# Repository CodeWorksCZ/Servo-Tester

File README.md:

# Servo Tester

> **Work In Progress (WIP):** This project is under active development.  
> Features, wiring, and behavior may change between commits.

RC servo tester for Arduino Pro Mini (ATmega328P, 16 MHz) with OLED UI, settings in EEPROM, and 3-channel current monitoring via INA3221.

User manual: `MANUAL.md`

## Features

- Servo control modes: `POT`, `CENTER`, `SWEEP`
- OLED screens: `STATUS`, `GAUGE`, `CURRENT`, `VBUS`, `PEAK`
- SWEEP cycle counter shown only in SWEEP mode
- Settings menu with EEPROM persistence
- INA3221 current measurement on 3 channels
- INA3221 bus voltage and droop (`dV`) view per channel
- INA3221 per-channel warning/critical current alerts (`WR`/`CR`)
- Optional alert LED output when any channel is in `WR` or `CR`
- Optional STD/HV mode indicator LEDs
- LED startup self-test
- Automatic unit display (`mA` / `A`) on current screens
- Servo rail mode detection (`STD` / `HV`) from ADC voltage sensing on `A1`
- Compile-time UI language selection through `include/config.h` and `include/lang.h`
- Minimal serial debug line for INA3221 communication check at boot

## Controls

- `SELECT` short press: switch LCD screen (`STATUS -> GAUGE -> CURRENT -> VBUS -> PEAK`)
- `SELECT` long press: enter settings menu
- `UP` / `DOWN` in status mode: change control mode (`POT`, `CENTER`, `SWEEP`)
- `UP` / `DOWN` in menu: navigate items or change value
- `SELECT` in menu: confirm

## Settings Menu

- `Min pulse` (us)
- `Max pulse` (us)
- `Reverse`
- `Sweep cycle` (0.5-10.0 s, default 3.0 s)
- `Burn cycles` (`0` = infinite SWEEP, otherwise stop after selected cycle count)
- `Save & exit`
- `Cancel`

## Pin Mapping (Default)

| Arduino Pin | Config Name | Function |
| --- | --- | --- |
| `D2` | `BTN_UP_PIN` | UP button |
| `D3` | `BTN_DOWN_PIN` | DOWN button |
| `D4` | `ALERT_LED_PIN` | Optional INA3221 warning/critical alert LED |
| `D5` | `BTN_SELECT_PIN` | SELECT button |
| `D6` | `SERVO_PIN` | Servo signal output |
| `D7` | `STD_MODE_LED_PIN` | STD servo rail indicator LED |
| `D8` | `HV_MODE_LED_PIN` | HV servo rail indicator LED |
| `D9` | `OLED_CLK` | OLED clock (`CLK` / `D0`) |
| `D10` | `OLED_MOSI` | OLED data (`MOSI` / `DIN` / `D1`) |
| `D11` | `OLED_RESET` | OLED reset |
| `D12` | `OLED_DC` | OLED data/command |
| `D13` | `OLED_CS` | OLED chip select |
| `A0` | `POT_PIN` | Servo control potentiometer |
| `A1` | `SERVO_VSENSE_PIN` | Servo rail voltage sensing through divider |
| `A4` | I2C `SDA` | INA3221 data |
| `A5` | I2C `SCL` | INA3221 clock |

Full mapping is in `pins.txt`.

## Configuration

Main configuration is in `include/config.h`.

You can adjust:

- UI language (`SERVO_TESTER_LANGUAGE`)
- pin assignments
- button debounce and long-press timing
- servo pulse limits and step size
- sweep timing and limits
- burn-in cycle count limits
- INA3221 shunt values and calibration factors
- ADC divider and HV threshold
- LED polarity and optional LED outputs

### UI Language

The UI language is selected at compile time to keep flash usage low:

```cpp
#define SERVO_TESTER_LANGUAGE SERVO_TESTER_LANG_EN
```

Available options:

- `SERVO_TESTER_LANG_EN`
- `SERVO_TESTER_LANG_CZ`

Text resources are stored in `include/lang.h`. Only the selected language is compiled into the firmware.

### Serial Debug

When `SERIAL_DEBUG_ENABLED` is enabled, the firmware prints one INA3221 status line after boot at `115200 baud`:

- `INA3221 OK`
- `INA3221 NOT FOUND`

This is intended only as a simple wiring/communication check.

## Build

PlatformIO environment:

- file: `platformio.ini`
- env: `pro16MHzatmega328`

Libraries used:

- Adafruit SSD1306
- Adafruit GFX Library
- Adafruit INA3221 Library
- Servo

## Project Layout

- `src/main.cpp`: entry point (`setup` / `loop`)
- `src/app_controller.*`: app state machine and high-level control flow
- `src/display_ui.*`: OLED rendering
- `src/ina_monitor.*`: INA3221 handling and peak tracking
- `src/button_input.*`: button debounce and short/long press events
- `src/settings_store.*`: EEPROM load/save/validation
- `src/app_types.h`: shared app structs/enums
- `hardware/Kicad/Servo Tester/`: KiCad project files for PCB/schematic
- `hardware/Schematics/`: exported schematic PDFs
- `hardware/Datasheets/`: component datasheets
- `hardware/enclosure/`: 3D printed enclosure files and notes

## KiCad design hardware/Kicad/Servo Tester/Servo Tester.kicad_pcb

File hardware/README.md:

# Hardware Notes (WIP)

This folder contains schematics/PCB files for the Servo Tester hardware.

## Pre-Layout Checklist

- Keep logic rail (`VCC` for Pro Mini + OLED + INA3221) separate from servo power rail.
- Do not feed logic directly from HV servo rail.
- Use a common GND, but route high-current servo return separately and join at one star point.

## Servo Power Protection

- Add bulk capacitor on servo rail input: `470-1000 uF` (low-ESR, voltage rating for your rail).
- Add local decoupling near each servo connector: `100 nF` from `+BATT` to `GND`.
- Add TVS diode across servo rail (`+BATT` to `GND`) near power entry.
- Add PTC fuse in series with servo rail input.

## INA3221 Current Measurement

- Place shunts in series with servo `+` path only.
- Route INA sense lines as Kelvin connections directly to shunt pads.
- For channels that may stay unconnected, add `100k` between `INx+` and `INx-` to reduce floating behavior.
- For `R100` shunts (`0.1 ohm`), keep alert thresholds below ~`1.64 A`.

## Servo Signal Robustness

- Add series resistor on each servo signal line: `220-470 ohm` (`330 ohm` recommended).
- Keep signal and GND return close together in routing/connectors.

## Connector Safety

- Prefer keyed/polarized connectors where possible.
- If using standard 3-pin servo headers, clearly mark `SIG`, `+`, `-` on silkscreen.

## Firmware-Coupled Pins (Current Config)

- `D6`: Servo PWM output
- `D4`: Alert LED output
- `A4/A5`: INA3221 I2C
- `A0`: Potentiometer input
- `A1`: Servo rail voltage sense

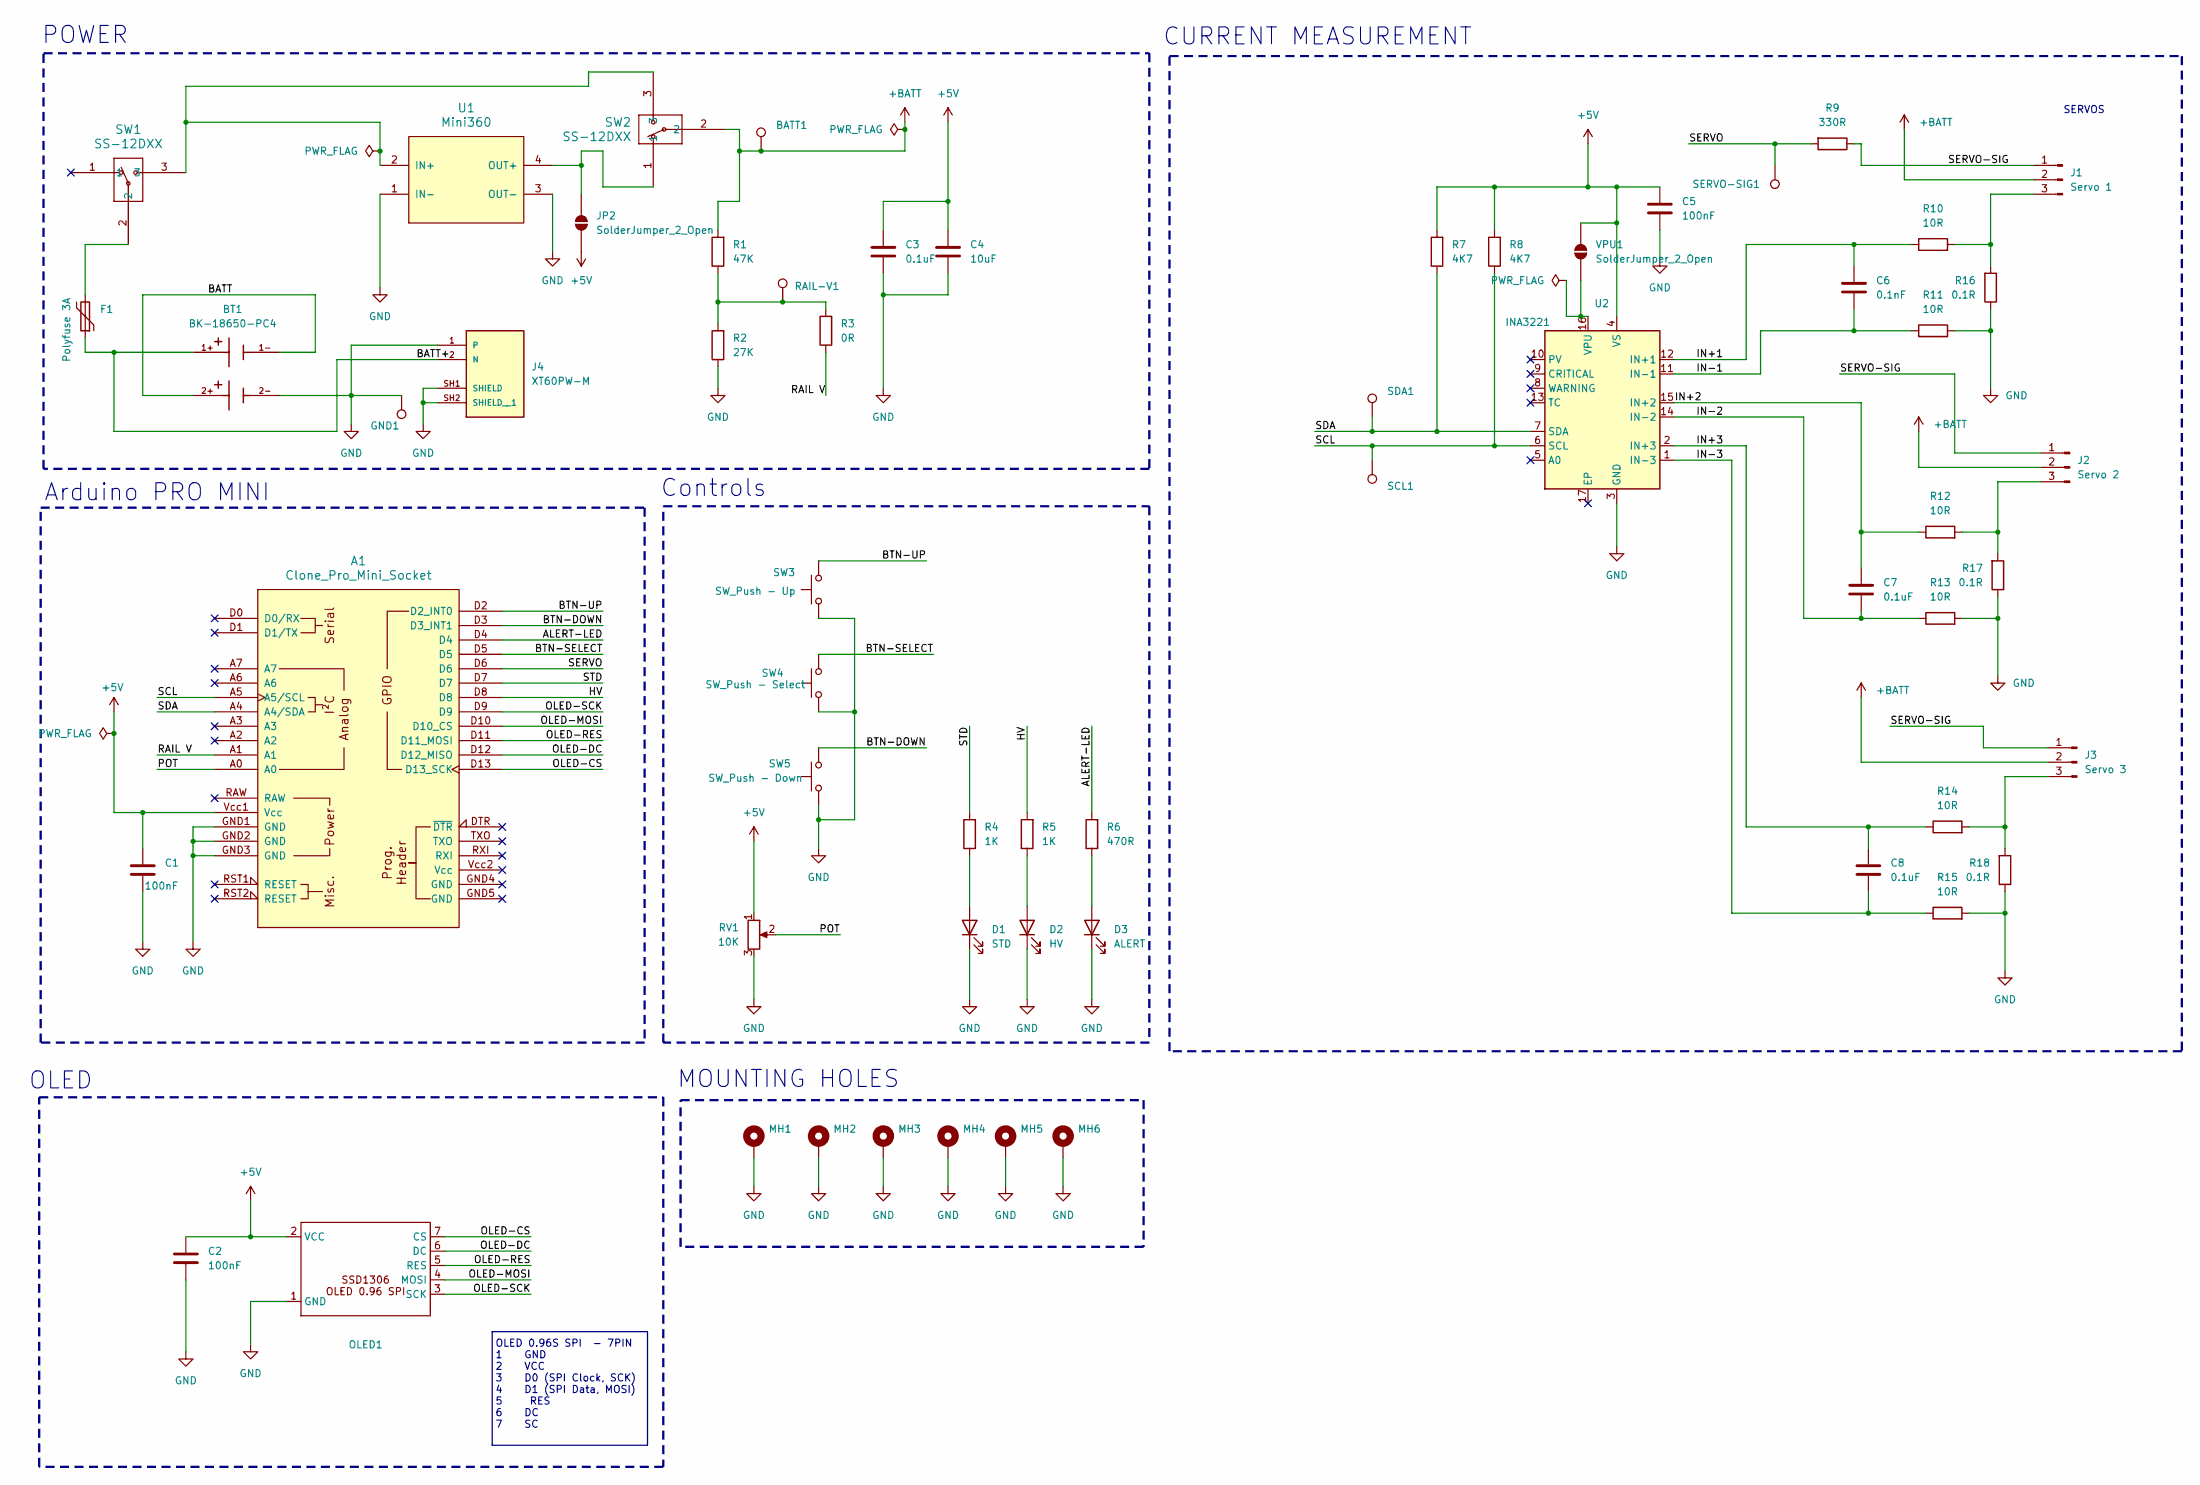
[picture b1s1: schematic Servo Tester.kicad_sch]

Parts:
A1: Clone_Pro_Mini_Socket; Clone_Pro_Mini_Socket_No_PROG
BATT1: TestPoint; TestPoint_Pad_D2.0mm
BT1: BK-18650-PC4; BAT_BK-18650-PC4; PARTREV K
C1, C2, C5: 100nF; C_0805_2012Metric
C3, C7, C8: 0.1uF; C_0805_2012Metric
C4: 10uF; C_0805_2012Metric
C6: 0.1nF; C_0805_2012Metric
D1: STD; LED_D3.0mm
D2: HV; LED_D3.0mm
D3: ALERT; LED_D3.0mm
F1: Polyfuse 3A; Fuse_LittleFuseRUEF300
GND1: TestPoint; TestPoint_Pad_D2.0mm
J1: Servo 1; PinHeader_1x03_P2.54mm_Horizontal
J2: Servo 2; PinHeader_1x03_P2.54mm_Horizontal
J3: Servo 3; PinHeader_1x03_P2.54mm_Horizontal
J4: XT60PW-M; AMASS_XT60PW-M_1x02_P7.20mm_Horizontal; PARTREV 1.2
JP2: SolderJumper_2_Open; SolderJumper-2_P1.3mm_Open_RoundedPad1.0x1.5mm
MH1, MH2, MH3, MH4, MH5, MH6: MountingHole_3.2mm_M3_Pad_Via
OLED1: OLED_0.96_SPI_Module_1x07_P2.54mm
R1: 47K; R_0805_2012Metric
R2: 27K; R_0805_2012Metric
R3: 0R; R_0805_2012Metric
R4, R5: 1K; R_0805_2012Metric
R6: 470R; R_0805_2012Metric
R7, R8: 4K7; R_0805_2012Metric
R9: 330R; R_0805_2012Metric
R10, R11, R12, R13, R14, R15: 10R; R_0805_2012Metric
R16, R17, R18: 0.1R; R_1210_3225Metric
RAIL-V1: TestPoint; TestPoint_Pad_D2.0mm
RV1: 10K; Potentiometer_Bourns_PTV09A-1_Single_Vertical
SCL1: TestPoint; TestPoint_Pad_D2.0mm
SDA1: TestPoint; TestPoint_Pad_D2.0mm
SERVO-SIG1: TestPoint; TestPoint_Pad_D2.0mm
SW1: SS-12DXX; SS12D11
SW2: SS-12DXX; SS12D10
SW3: SW_Push - Up; SW_PUSH_6mm_H8.5mm
SW4: SW_Push - Select; SW_PUSH_6mm_H8.5mm
SW5: SW_Push - Down; SW_PUSH_6mm_H8.5mm
U1: Mini360; Ultra Mini-360
U2: INA3221; INA3221_VQFN-16_4x4mm_P0.65mm_EP2.6x2.6mm
VPU1: SolderJumper_2_Open; SolderJumper-2_P1.3mm_Open_RoundedPad1.0x1.5mm

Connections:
+5V: A1.Vcc1 (Vcc), C1.1, C2.1, C3.1, C4.1, C5.1, JP2.1 (A), OLED1.2 (VCC), R7.2, R8.2, RV1.1, U2.4 (VS), VPU1.2 (B)
+BATT: BATT1.1 (1_1), J1.2, J2.2, J3.2, R1.2, SW2.2
/ALERT-LED: A1.D4, R6.2
/BATT: BT1.1-, BT1.2+
/BATT+: BT1.1+, F1.1, J4.2 (N)
/BTN-DOWN: A1.D3 (D3_INT1), SW5.2
/BTN-SELECT: A1.D5, SW4.2
/BTN-UP: A1.D2 (D2_INT0), SW3.2
/HV: A1.D8, R5.2
/IN+1: C6.1, R10.1, U2.12 (IN+1)
/IN+2: C7.1, R12.1, U2.15 (IN+2)
/IN+3: C8.1, R14.1, U2.2 (IN+3)
/IN-1: C6.2, R11.1, U2.11 (IN-1)
/IN-2: C7.2, R13.1, U2.14 (IN-2)
/IN-3: C8.2, R15.1, U2.1 (IN-3)
/OLED-CS: A1.D13 (D13_SCK), OLED1.7 (CS)
/OLED-DC: A1.D12 (D12_MISO), OLED1.6 (DC)
/OLED-MOSI: A1.D10 (D10_CS), OLED1.4 (MOSI)
/OLED-RES: A1.D11 (D11_MOSI), OLED1.5 (RES)
/OLED-SCK: A1.D9, OLED1.3 (SCK)
/POT: A1.A0, RV1.2
/RAIL V: A1.A1, R3.1
/SCL: A1.A5 (A5/SCL), R8.1, SCL1.1 (1_1), U2.6 (SCL)
/SDA: A1.A4 (A4/SDA), R7.1, SDA1.1 (1_1), U2.7 (SDA)
/SERVO: A1.D6, R9.2, SERVO-SIG1.1 (1_1)
/SERVO-SIG: J1.1, J2.1, J3.1, R9.1
/STD: A1.D7, R4.2
GND: A1.GND1 (GND), A1.GND2 (GND), A1.GND3 (GND), BT1.2-, C1.2, C2.2, C3.2, C4.2, C5.2, D1.1 (K), D2.1 (K), D3.1 (K), GND1.1 (1_1), J4.1, J4.SH1 (SHIELD), J4.SH2 (SHIELD__1), MH1.1 (1_1), MH2.1 (1_1), MH3.1 (1_1), MH4.1 (1_1), MH5.1 (1_1), MH6.1 (1_1), OLED1.1 (GND), R2.1, R11.2, R13.2, R15.2, R16.1, R17.1, R18.1, RV1.3, SW3.1, SW4.1, SW5.1, U1.1 (IN-), U1.3 (OUT-), U2.3 (GND)
unnamed: D1.2 (A), R4.1
unnamed: D2.2 (A), R5.1
unnamed: D3.2 (A), R6.1
unnamed: F1.2, SW1.2
unnamed: J1.3, R10.2, R16.2
unnamed: J2.3, R12.2, R17.2
unnamed: J3.3, R14.2, R18.2
unnamed: JP2.2 (B), SW2.1, U1.4 (OUT+)
unnamed: R1.1, R2.2, R3.2, RAIL-V1.1 (1_1)
unnamed: SW1.3, SW2.3, U1.2 (IN+)
unnamed: U2.16 (VPU), VPU1.1 (A)

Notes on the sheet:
CURRENT MEASUREMENT
Controls
Arduino PRO MINI
POWER
OLED
MOUNTING HOLES
SERVOS
OLED 0.96S SPI - 7PIN 1 GND 2 VCC 3 D0 (SPI Clock, SCK) 4 D1 (SPI Data, MOSI) 5 RES 6 DC 7 SC

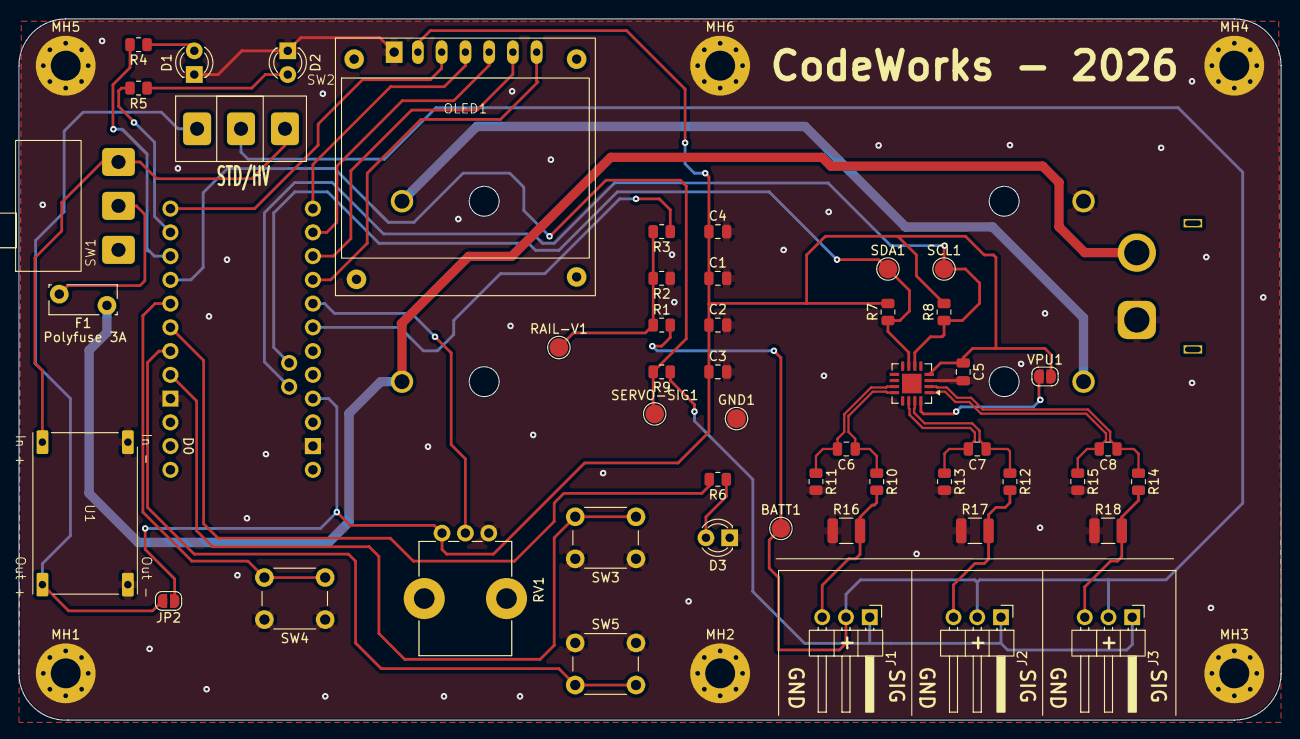
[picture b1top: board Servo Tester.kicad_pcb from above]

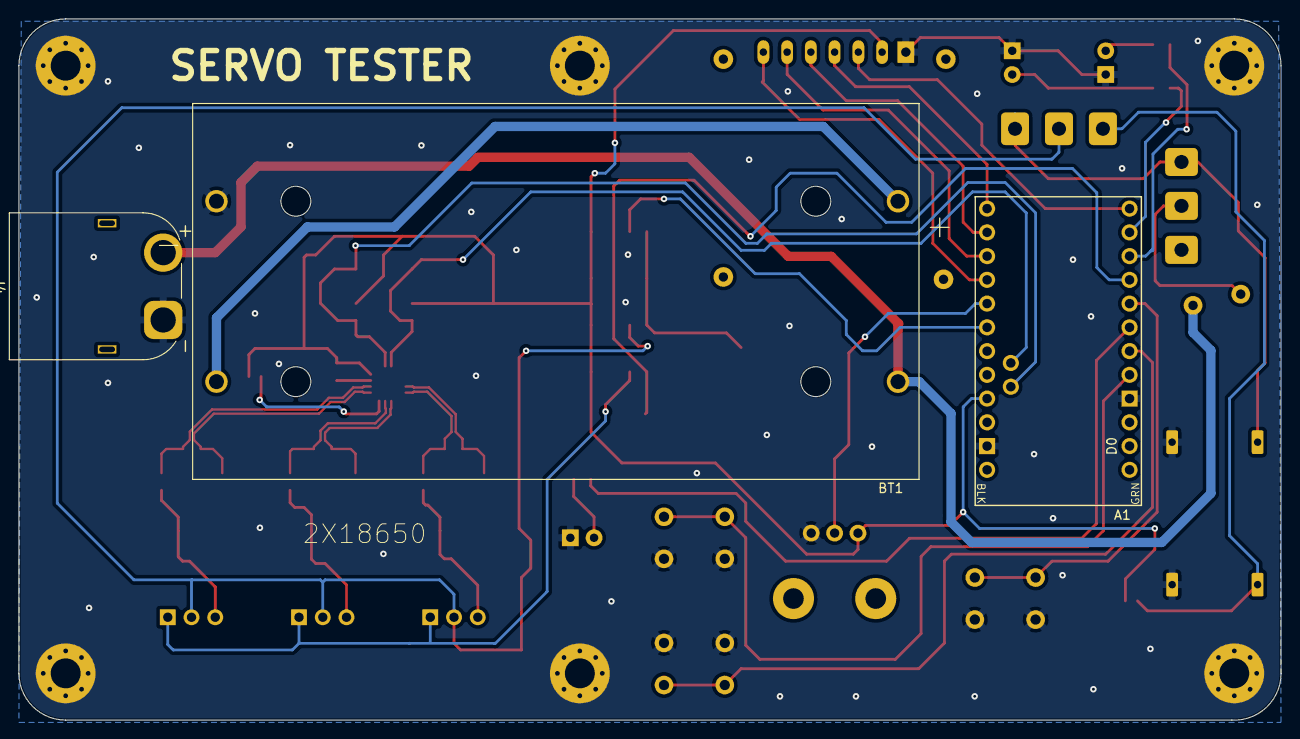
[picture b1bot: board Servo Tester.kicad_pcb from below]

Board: 2 copper layers, 135.0 x 75.0 mm, 59 parts (3 on the bottom side), 39 nets.

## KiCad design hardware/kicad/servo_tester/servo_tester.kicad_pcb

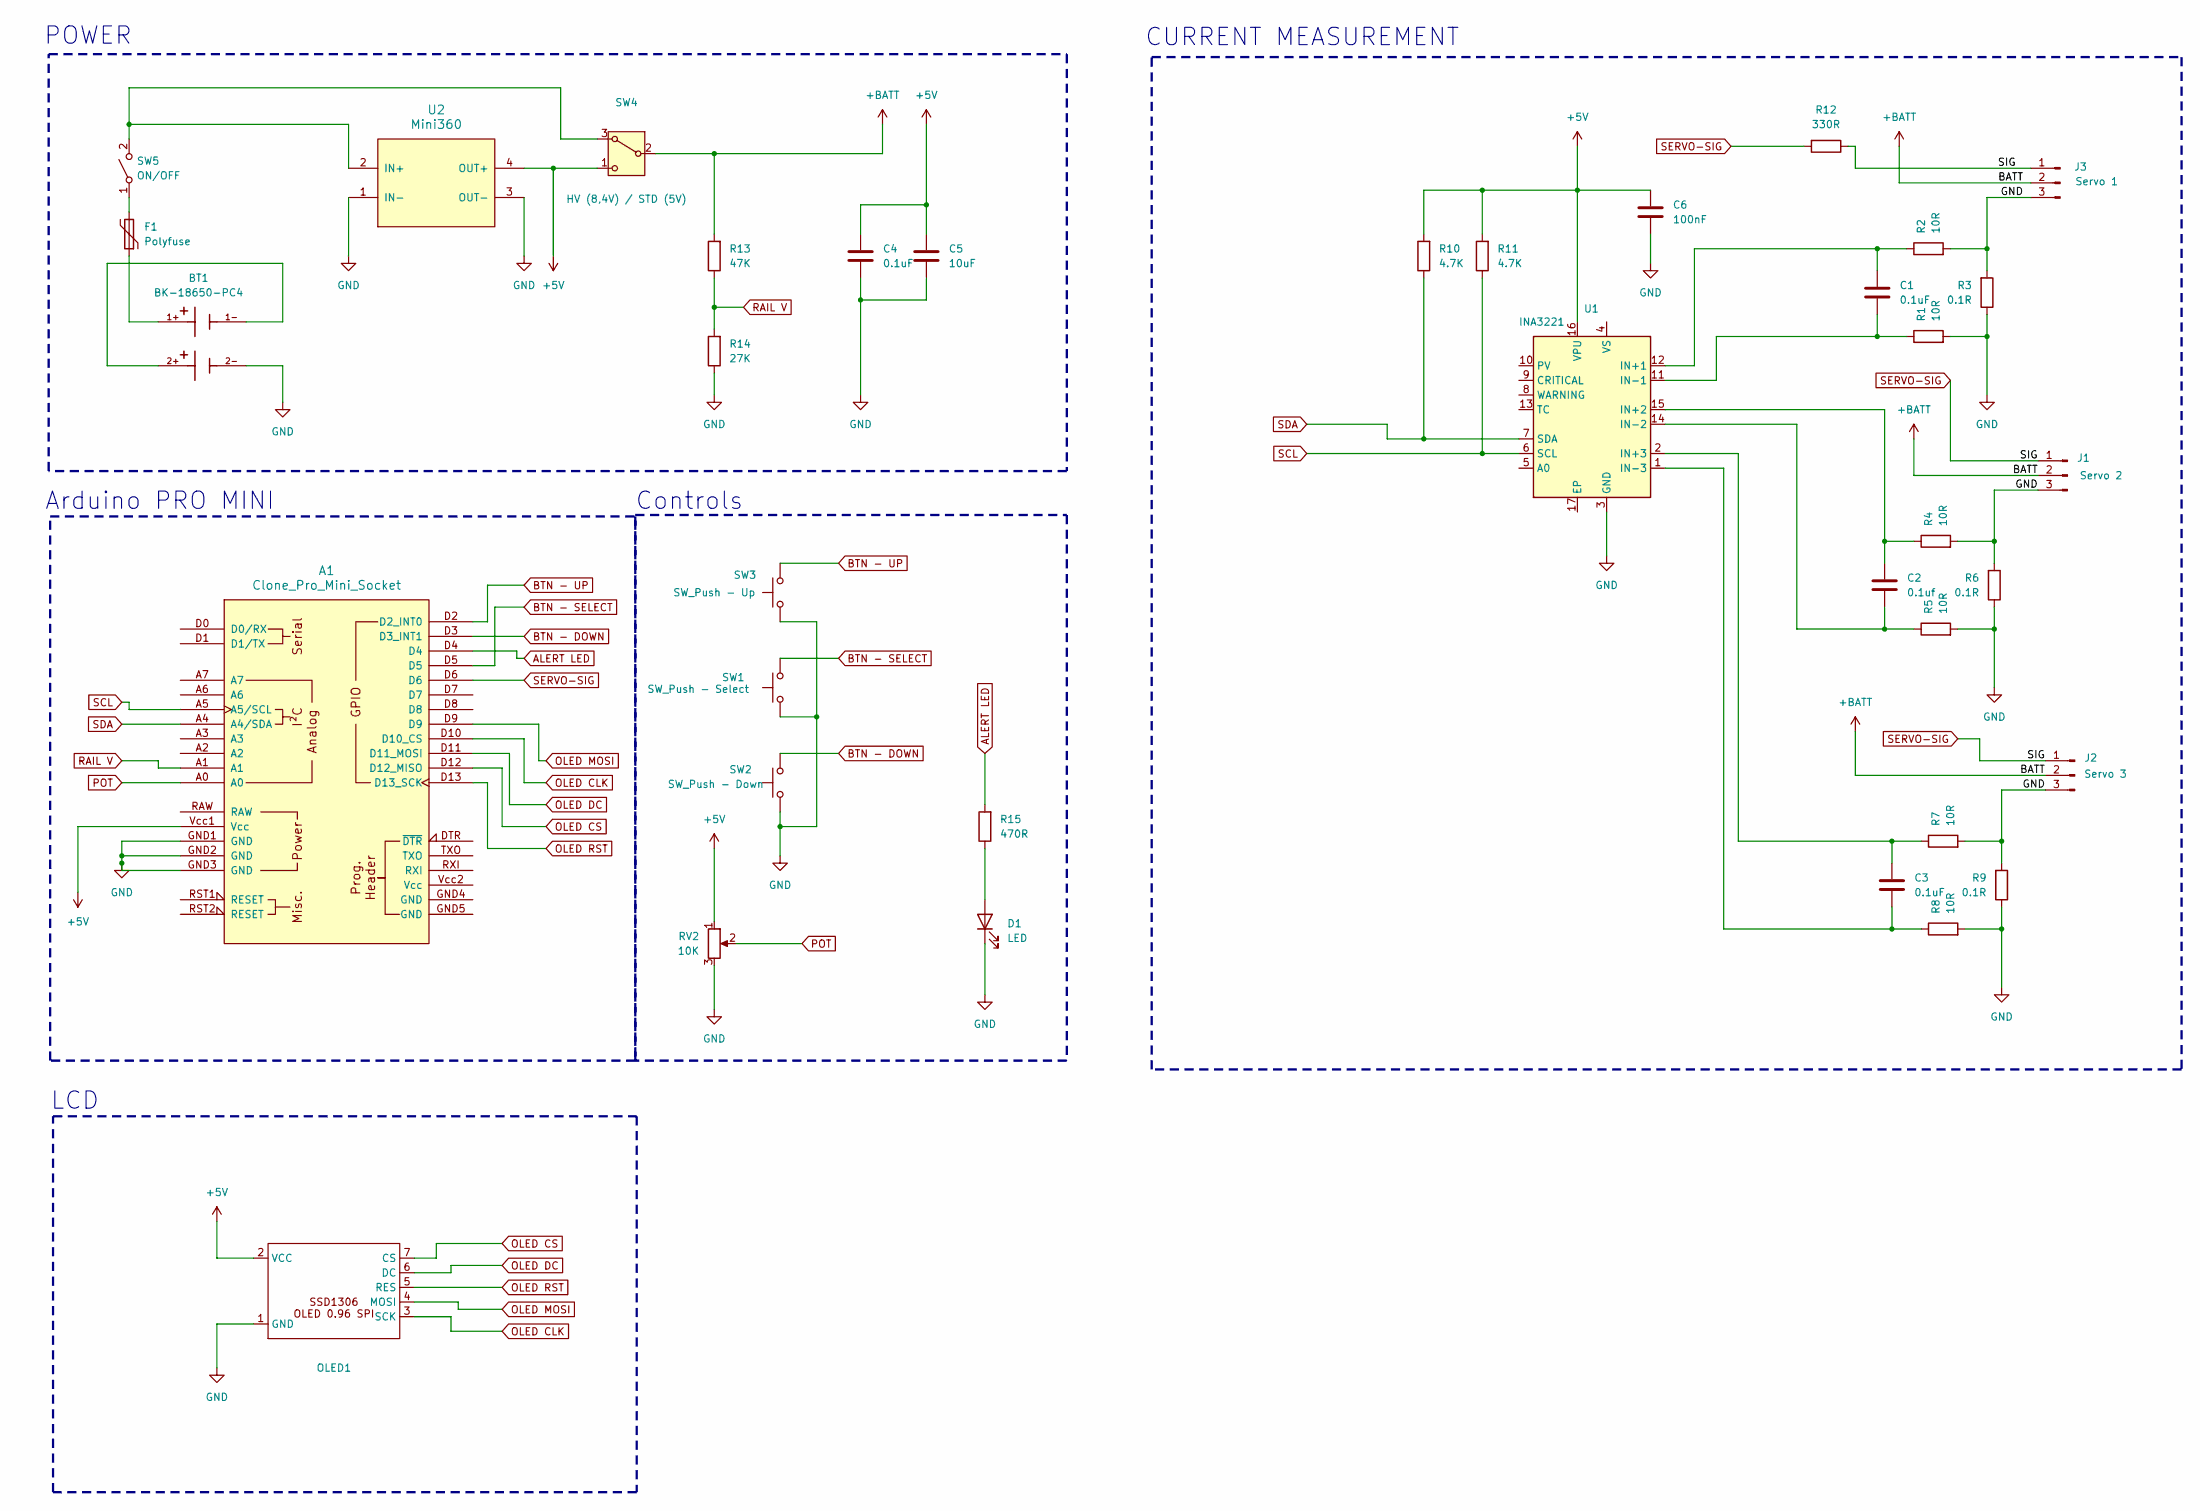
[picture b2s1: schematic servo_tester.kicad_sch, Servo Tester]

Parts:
A1: Clone_Pro_Mini_Socket
BT1: BK-18650-PC4; BAT_BK-18650-PC4; PARTREV K
C1, C3, C4: 0.1uF; C_0603_1608Metric
C2: 0.1uf; C_0603_1608Metric
C5: 10uF; C_0603_1608Metric
C6: 100nF; C_0603_1608Metric
D1: LED; LED_D3.0mm
F1: Polyfuse; Fuse_Bourns_MF-RG300
J1: Servo 2; PinHeader_1x03_P2.54mm_Vertical
J2: Servo 3; PinHeader_1x03_P2.54mm_Vertical
J3: Servo 1; PinHeader_1x03_P2.54mm_Vertical
OLED1: OLED_0.96_SPI_Module_1x07_P2.54mm
R1, R2, R4, R5, R7, R8: 10R; R_0603_1608Metric
R3, R6, R9: 0.1R; R_1210_3225Metric
R10, R11: 4.7K; R_0603_1608Metric
R12: 330R; R_0603_1608Metric
R13: 47K; R_0603_1608Metric
R14: 27K; R_0603_1608Metric
R15: 470R; R_0603_1608Metric
RV2: 10K; Potentiometer_Bourns_PTV09A-1_Single_Vertical
SW1: SW_Push - Select; SW_PUSH_6mm
SW2: SW_Push - Down; SW_PUSH_6mm
SW3: SW_Push - Up; SW_PUSH_6mm
SW4: HV (8,4V) / STD (5V); SW_XKB_DM1-16UD-1
SW5: ON/OFF
U1: INA3221; Texas_RGV0016A_VQFN-16-1EP_4x4mm_P0.65mm_EP2.1x2.1mm
U2: Mini360; Ultra Mini-360

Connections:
+5V: A1.Vcc1 (Vcc), C4.1, C5.1, C6.1, OLED1.2 (VCC), R10.2, R11.2, RV2.1, SW4.1 (C), U1.16 (VPU), U2.4 (OUT+)
+BATT: J1.2, J2.2, J3.2, R13.2, SW4.2 (B)
ALERT LED: A1.D4, R15.2
BTN - DOWN: A1.D3 (D3_INT1), SW2.2
BTN - SELECT: A1.D5, SW1.2
BTN - UP: A1.D2 (D2_INT0), SW3.2
GND: A1.GND1 (GND), A1.GND2 (GND), A1.GND3 (GND), BT1.2-, C4.2, C5.2, C6.2, D1.1 (K), J1.3, J2.3, J3.3, OLED1.1 (GND), R1.2, R2.2, R3.1, R3.2, R4.2, R5.2, R6.1, R6.2, R7.2, R8.2, R9.1, R9.2, R14.1, RV2.3, SW1.1, SW2.1, SW3.1, U1.3 (GND), U2.1 (IN-), U2.3 (OUT-)
unnamed: BT1.1+, F1.1
unnamed: BT1.1-, BT1.2+
unnamed: D1.2 (A), R15.1
unnamed: SW4.3 (A), SW5.2 (B), U2.2 (IN+)
unnamed: F1.2, SW5.1 (A)
unnamed: C1.1, R2.1, U1.12 (IN+1)
unnamed: C2.1, R4.1, U1.15 (IN+2)
unnamed: C3.1, R7.1, U1.2 (IN+3)
unnamed: C1.2, R1.1, U1.11 (IN-1)
unnamed: C2.2, R5.1, U1.14 (IN-2)
unnamed: C3.2, R8.1, U1.1 (IN-3)
OLED CLK: A1.D10 (D10_CS), OLED1.3 (SCK)
OLED CS: A1.D12 (D12_MISO), OLED1.7 (CS)
OLED DC: A1.D11 (D11_MOSI), OLED1.6 (DC)
OLED MOSI: A1.D9, OLED1.4 (MOSI)
OLED RST: A1.D13 (D13_SCK), OLED1.5 (RES)
POT: A1.A0, RV2.2
RAIL V: A1.A1, R13.1, R14.2
SCL: A1.A5 (A5/SCL), R11.1, U1.6 (SCL)
SDA: A1.A4 (A4/SDA), R10.1, U1.7 (SDA)
SERVO-SIG: A1.D6, J1.1, J2.1, J3.1, R12.1, R12.2

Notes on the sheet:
CURRENT MEASUREMENT
Controls
Arduino PRO MINI
POWER
LCD

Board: 2 copper layers, 36 parts (1 on the bottom side), 27 nets, no tracks yet.

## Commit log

2026-02-16 Add OLED settings menu, central config header, and README docs
2026-02-16 docs: rewrite README in English
2026-02-16 docs: fix markdownlint spacing in README
2026-02-16 Refine config usage and add English code comments
2026-02-16 Refactor app modules, add sweep counter UI, and refresh README
2026-02-16 Reorganize project to root layout and introduce AppController
2026-02-16 Add code comments, mark README as WIP, and include KiCad hardware files
2026-02-16 Add VBUS screen, INA3221 alerts, and smoother display values
2026-02-16 Add alert LED output for INA warning/critical states
2026-02-16 Tune INA3221 averaging and conversion timing
2026-02-19 Update sweep settings and ignore KiCad lock/cache artifacts
2026-02-19 Normalize KiCad folder path without spaces
2026-02-19 Update README hardware layout and ignore legacy KiCad path
2026-02-23 Update OLED pin mapping and sync hardware files
2026-02-23 Switch KiCad project path back to hardware/Kicad/Servo Tester
2026-04-10 Add designators, netlist, positions, and symbol library for Servo Tester project
    - Created designators.csv to define component designators for the Servo Tester.
    - Added netlist.ipc to specify the electrical connections and layout of the circuit.
    - Introduced positions.csv to provide the coordinates and rotation for each component on the PCB.
    - Established sym-lib-table to include the Servo Tester symbol library in KiCad.
2026-04-10 Mark subproject as dirty in KiCad history
2026-04-10 Ignore .history directory
2026-04-10 Update hardware assets and README
2026-04-10 Translate user manual to English
2026-04-10 Add 3D model of PCB for Servo Tester project
2026-04-29 feat: Add language selection and improve UI for servo tester
    - Introduced compile-time language selection for English and Czech.
    - Updated UI strings to use language-specific definitions.
    - Added support for optional power mode indicator LEDs.
    - Implemented burn cycles feature to limit servo sweep cycles.
    - Enhanced settings storage and validation for new burn cycles parameter.
    - Improved serial debug output for INA3221 communication checks.
2026-04-29 docs: Update user manual and README with new features and language selection
